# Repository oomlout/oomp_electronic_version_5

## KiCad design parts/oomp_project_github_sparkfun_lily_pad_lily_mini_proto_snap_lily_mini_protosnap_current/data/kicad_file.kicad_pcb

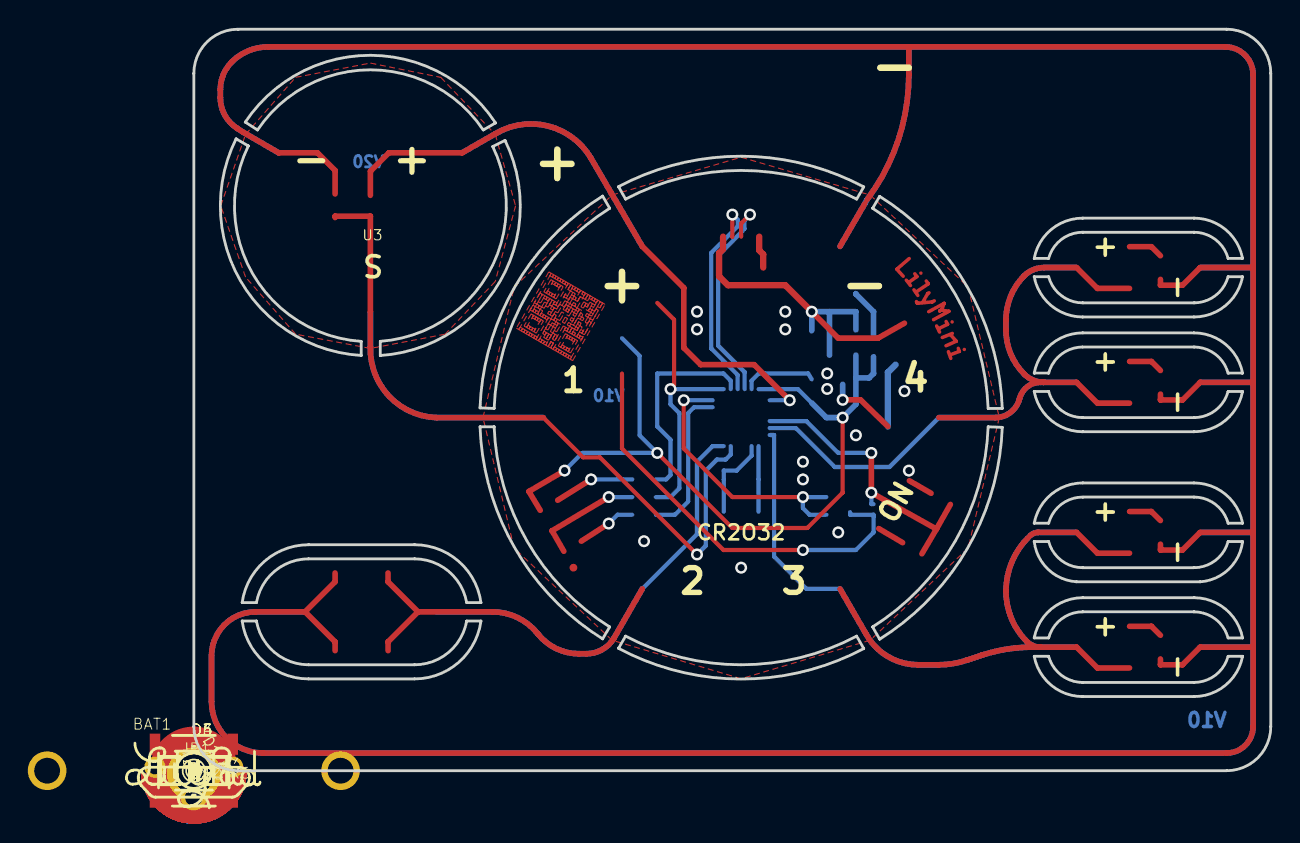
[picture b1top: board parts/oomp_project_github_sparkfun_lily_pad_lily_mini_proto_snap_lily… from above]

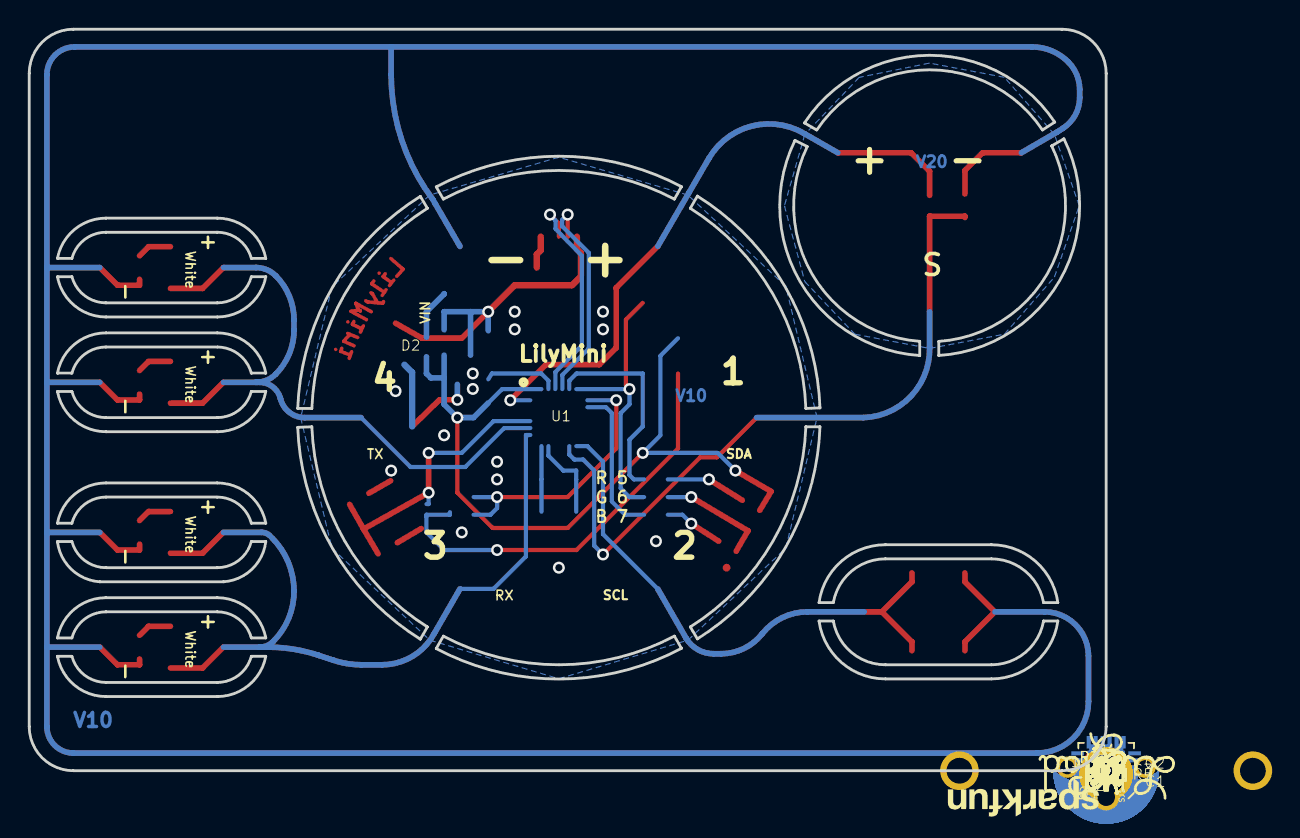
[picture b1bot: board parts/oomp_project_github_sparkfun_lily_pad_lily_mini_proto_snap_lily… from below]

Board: 2 copper layers, 77.5 x 53.3 mm, 170 parts (35 on the bottom side), 27 nets.

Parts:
$1_61_$_2016-09-25_21-56-09: OSHW-LOGOS; OSHW-LOGO-S
BAT1: CR2032; BATTERY_20MM_PTH_KIT
C1, C2: 15pF; 0603-CAP
C3, C4: 0.1uF; 0603-CAP
D1: P-LCC-4-3
D2: RB751; SOD-523
D3, D4, D5, D6: LED-1206
FD1, FD2, FD3, FD4: FIDUCIAL1X2; FIDUCIAL-1X2
FRAME1: FRAME-LETTER; CREATIVE_COMMONS
JP1: USB-B-MICRO-SMD_VERT
JP2: 1X01NS
JP3: 1X01_POGOPIN_PAD_NOSILK_1SIDE_SQUARE
JP4, JP5, JP6, JP7, JP8, JP9: 1X01_POGOPIN_PAD_NOSILK_1SIDE_ROUND
JP12, JP13: PETAL-MEDIUM-2SIDE
JP20, JP21, JP22, JP23, JP24, JP25, JP26, JP27: PETAL-SMALL-2SIDE
LOGO1: LOGO-L
LOGO2: LOGO-L-TOP
LOGO3: OSHW-LOGOS; OSHW-LOGO-S
LOGO4: SFE_LOGO_NAME.1_INCH; SFE_LOGO_NAME_.1
Q1: ZXMP6A13F; SOT23-3
R1, R6: 10K; 0603-RES
R2, R5: 330; 0603-RES
R3: 2K; 0603-RES
R4: 1K; 0603-RES
R7, R8, R9, R10: 150; 0603-RES
S1: TACTILE_SWITCH_SMD_4.6X2.8MM
S2: TACTILE-SWITCH-SMD
SEWTAP1, SEWTAP2, SEWTAP3, SEWTAP4: PETAL-MEDIUM-2SIDE
SEWTAP+0: PETAL-MEDIUM-2SIDE
SEWTAP-0: PETAL-MEDIUM-2SIDE
SEWTAPLS+0: PLUS; PETAL-SMALL-2SIDE
SEWTAPLS-0: MINUS; PETAL-SMALL-2SIDE
SEWTAPLSOUT0: OUT; PETAL-SMALL-2SIDE
SJ1: PAD-JUMPER-2-NO_NO_SILK
ST1, ST2, ST3: PETAL-NOHOLE-2SIDE
U1: SAMD11D14A-M; QFN-24_ALT2
U2: AP2112K-3.3V; SOT23-5
U3: ALS-PT19
U$1: LOGO-LILYPAD
U$2: LOGO-LPLP; LOGO-LILYPAD
U$4: SFE_LOGO_FLAME_COPPER_EXPOSED_.1
U$5, U$6, U$7, U$8, U$9: LOGO-L
UNK_HOLE_0: dummyfp0
UNK_HOLE_1: dummyfp1
UNK_HOLE_2: dummyfp2
UNK_HOLE_3: dummyfp3
UNK_HOLE_4: dummyfp4
UNK_HOLE_5: dummyfp5
UNK_HOLE_6: dummyfp6
UNK_HOLE_7: dummyfp7
UNK_HOLE_8: dummyfp8
UNK_HOLE_9: dummyfp9
UNK_HOLE_10: dummyfp10
UNK_HOLE_11: dummyfp11
UNK_HOLE_12: dummyfp12
UNK_HOLE_13: dummyfp13
UNK_HOLE_14: dummyfp14
UNK_HOLE_15: dummyfp15
UNK_HOLE_16: dummyfp16
UNK_HOLE_17: dummyfp17
UNK_HOLE_18: dummyfp18
UNK_HOLE_19: dummyfp19
UNK_HOLE_20: dummyfp20
UNK_HOLE_21: dummyfp21
UNK_HOLE_22: dummyfp22
UNK_HOLE_23: dummyfp23
UNK_HOLE_24: dummyfp24
UNK_HOLE_25: dummyfp25
UNK_HOLE_26: dummyfp26
UNK_HOLE_27: dummyfp27
UNK_HOLE_28: dummyfp28
UNK_HOLE_29: dummyfp29
UNK_HOLE_30: dummyfp30
UNK_HOLE_31: dummyfp31
UNK_HOLE_32: dummyfp32
UNK_HOLE_33: dummyfp33
UNK_HOLE_34: dummyfp34
UNK_HOLE_35: dummyfp35
UNK_HOLE_36: dummyfp36
UNK_HOLE_37: dummyfp37
UNK_HOLE_38: dummyfp38
UNK_HOLE_39: dummyfp39
UNK_HOLE_40: dummyfp40
UNK_HOLE_41: dummyfp41
UNK_HOLE_42: dummyfp42
UNK_HOLE_43: dummyfp43
UNK_HOLE_44: dummyfp44
UNK_HOLE_45: dummyfp45
UNK_HOLE_46: dummyfp46
UNK_HOLE_47: dummyfp47
UNK_HOLE_48: dummyfp48
UNK_HOLE_49: dummyfp49
UNK_HOLE_50: dummyfp50
UNK_HOLE_51: dummyfp51
UNK_HOLE_52: dummyfp52
UNK_HOLE_53: dummyfp53
UNK_HOLE_54: dummyfp54
UNK_HOLE_55: dummyfp55
UNK_HOLE_56: dummyfp56
UNK_HOLE_57: dummyfp57
UNK_HOLE_58: dummyfp58
UNK_HOLE_59: dummyfp59
UNK_HOLE_60: dummyfp60
UNK_HOLE_61: dummyfp61
UNK_HOLE_62: dummyfp62
UNK_HOLE_63: dummyfp63
UNK_HOLE_64: dummyfp64
UNK_HOLE_65: dummyfp65
UNK_HOLE_66: dummyfp66
UNK_HOLE_67: dummyfp67
UNK_HOLE_68: dummyfp68
UNK_HOLE_69: dummyfp69
UNK_HOLE_70: dummyfp70
UNK_HOLE_71: dummyfp71
UNK_HOLE_72: dummyfp72
UNK_HOLE_73: dummyfp73
UNK_HOLE_74: dummyfp74
UNK_HOLE_75: dummyfp75
UNK_HOLE_76: dummyfp76
UNK_HOLE_77: dummyfp77
UNK_HOLE_78: dummyfp78
UNK_HOLE_79: dummyfp79
UNK_HOLE_80: dummyfp80
UNK_HOLE_81: dummyfp81
UNK_HOLE_82: dummyfp82
UNK_HOLE_83: dummyfp83
UNK_HOLE_84: dummyfp84
UNK_HOLE_85: dummyfp85
UNK_HOLE_86: dummyfp86
UNK_HOLE_87: dummyfp87
UNK_HOLE_88: dummyfp88
UNK_HOLE_89: dummyfp89
UNK_HOLE_90: dummyfp90
UNK_HOLE_91: dummyfp91
Y1: 32.768kHz; CRYSTAL-SMD-3.2X1.5MM

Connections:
B: D1.3, R2.2
BATT3V: BAT1.+1, BAT1.+2, JP9.P$1, Q1.3
BUTTON: S1.1, S1.2, SJ1.1, U1.4
G: D1.2, R3.2
GND: BAT1.-3, C1.1, C2.1, C3.2, C4.2, JP1.GND, JP4.P$1, JP13.1, JP21.1, JP23.1, JP25.1, JP27.1, R1.1, R6.1, R7.1, R8.1, R9.1, R10.1, S1.3, S1.4, S2.3, S2.4, SEWTAP-0.1, SEWTAPLS-0.1, U1.23, U2.2
unnamed: D2.A, U2.5
unnamed: D3.C, R7.2
unnamed: D4.C, R8.2
unnamed: D5.C, R9.2
unnamed: D6.C, R10.2
R: D1.1, R4.2
SEWTAP1: R6.2, SEWTAP1.1, SEWTAPLSOUT0.1, U1.11, U3.E
SEWTAP2: JP12.1, S2.1, S2.2, SEWTAP2.1, U1.12
SEWTAP3: D3.A, D4.A, JP20.1, JP22.1, SEWTAP3.1, U1.6
SEWTAP4: D5.A, D6.A, JP24.1, JP26.1, SEWTAP4.1, U1.5
SEWTAP+: SEWTAP+0.1, SEWTAPLS+0.1, U1.1, U3.C
USB5V: JP1.VBUS, JP2.1, Q1.1, R1.2, U2.1, U2.3
USB_N: JP1.D-, U1.21
USB_P: JP1.D+, U1.22
VDD: C4.1, D1.4, D2.C, JP6.P$1, Q1.2, U1.24
X1: C1.2, U1.7, Y1.P$2
X2: C2.2, U1.8, Y1.P$1
~BLUE/SWDIO: JP7.P$1, R2.1, U1.20
~GREEN: R3.1, U1.17
~RED/SWDCLK: JP3.P$1, R4.1, U1.19
~RST: JP8.P$1, R5.2, SJ1.2
~RST1: C3.1, R5.1, U1.18

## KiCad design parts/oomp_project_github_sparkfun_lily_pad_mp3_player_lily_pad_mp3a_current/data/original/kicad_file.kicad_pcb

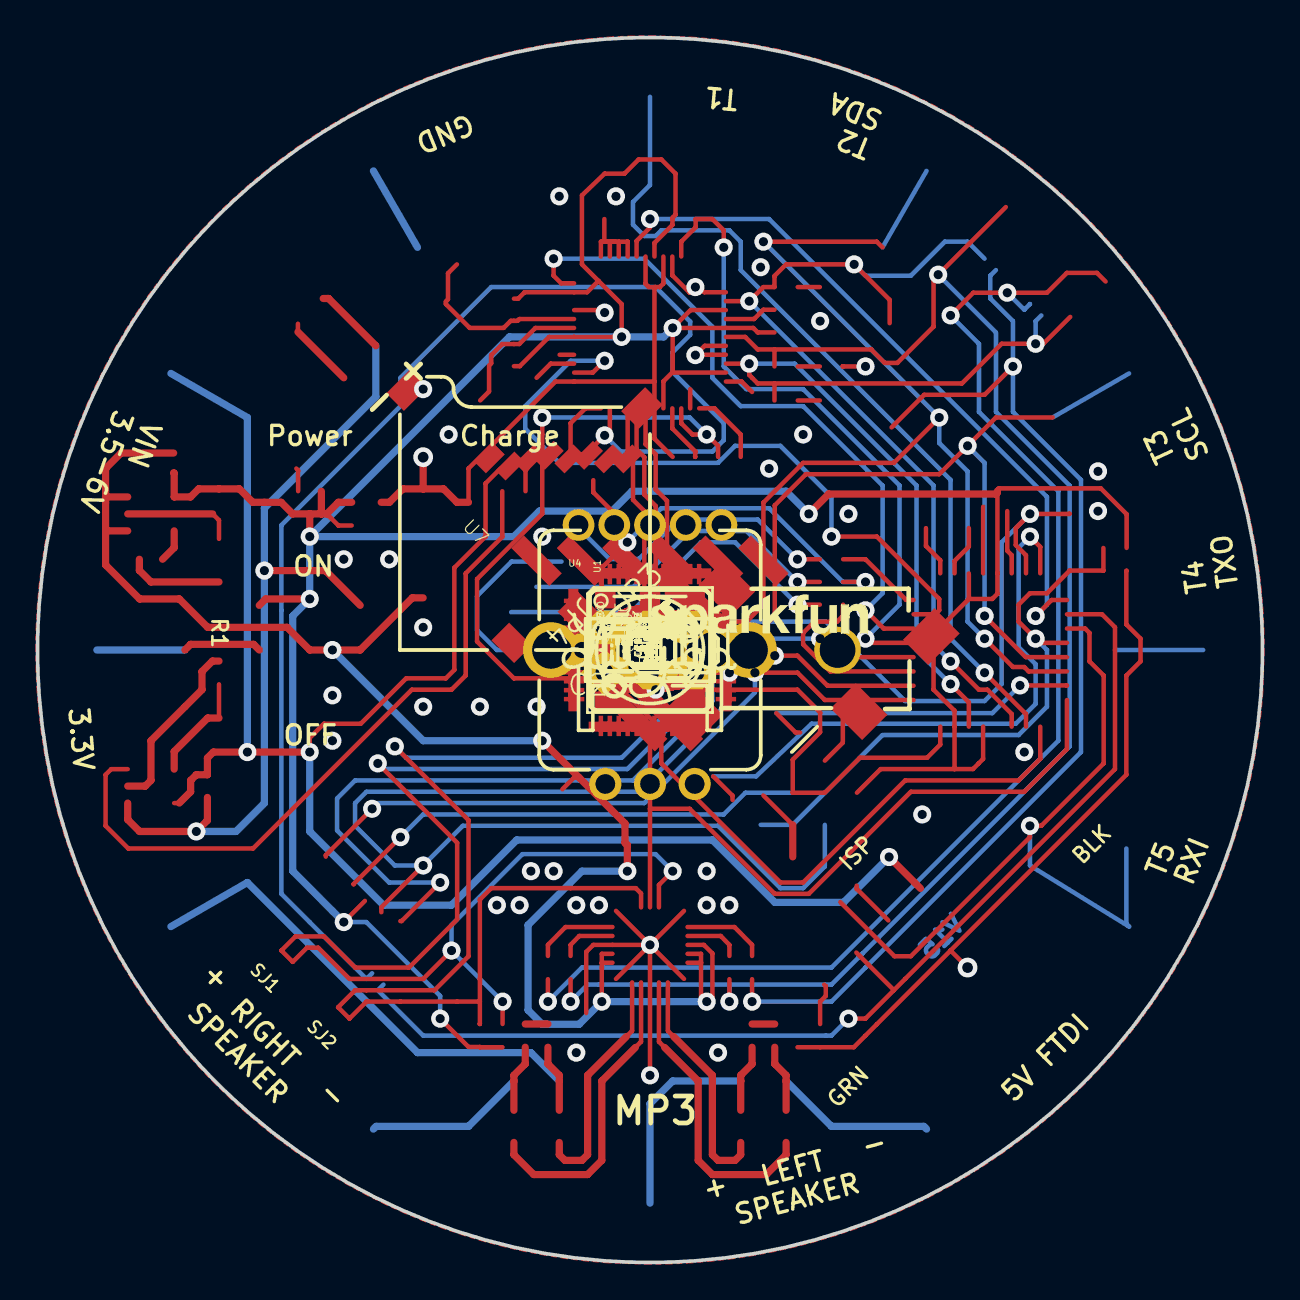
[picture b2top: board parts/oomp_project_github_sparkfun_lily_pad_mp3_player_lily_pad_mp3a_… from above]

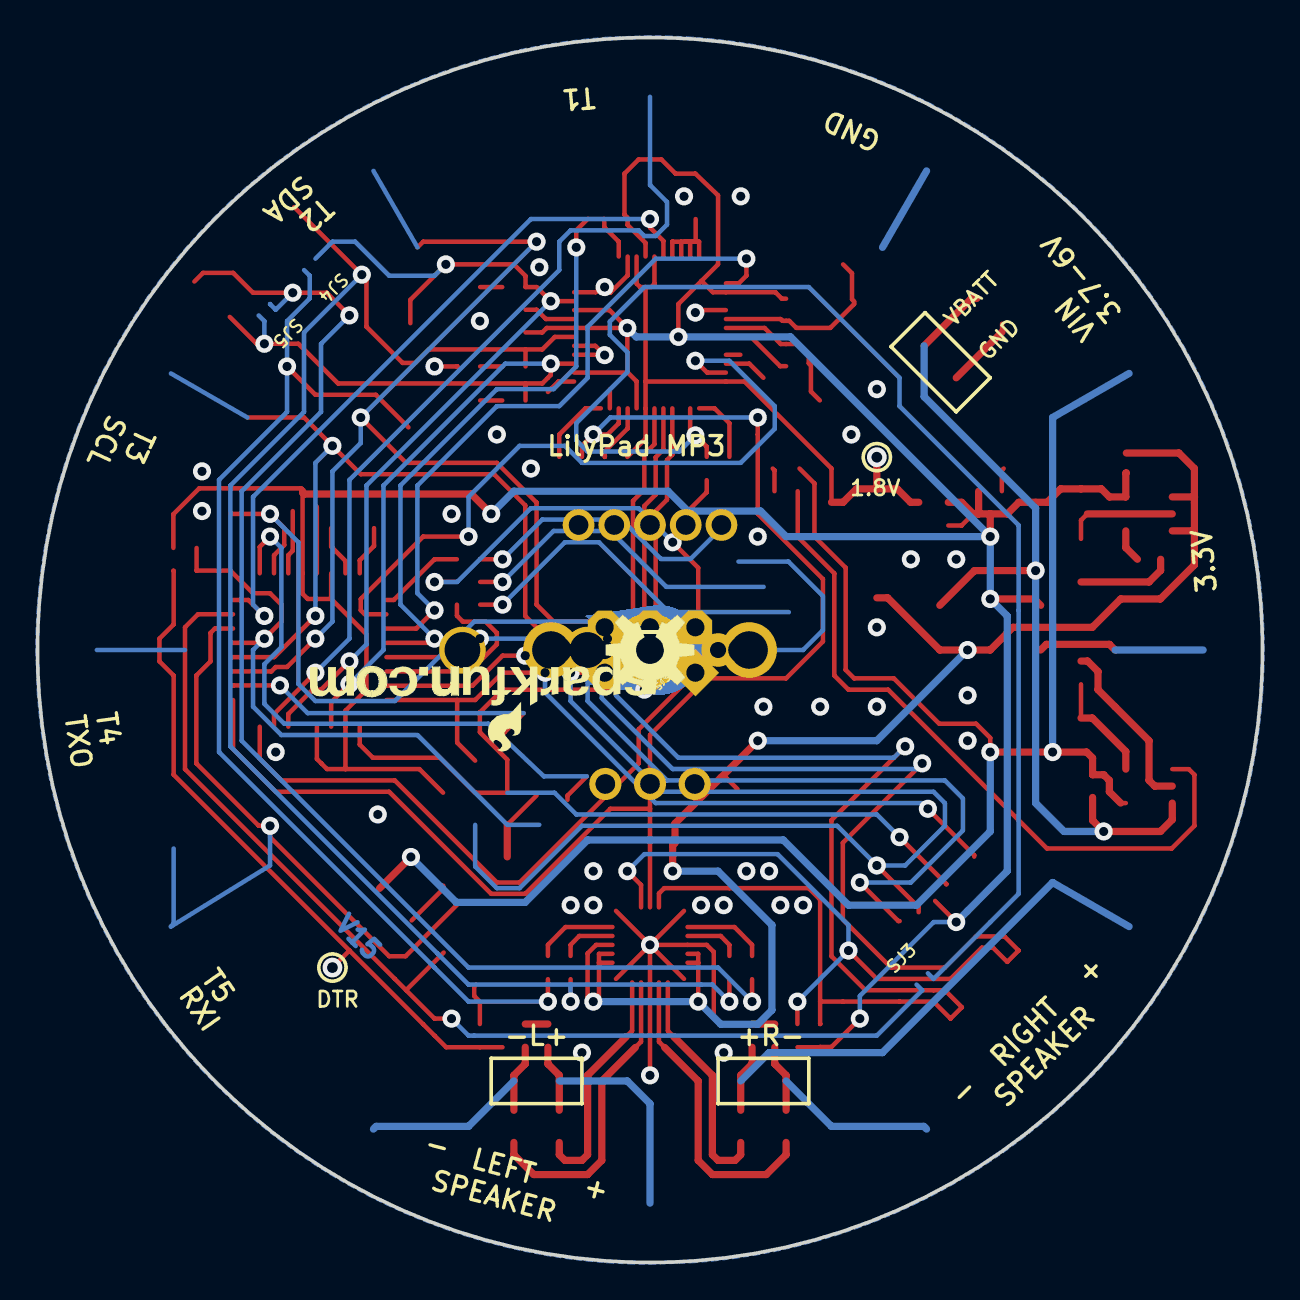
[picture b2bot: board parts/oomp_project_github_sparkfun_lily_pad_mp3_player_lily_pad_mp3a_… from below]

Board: 2 copper layers, 68.6 x 68.6 mm, 121 parts (7 on the bottom side), 69 nets.

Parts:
C1, C4, C6, C8, C18, C19, C20, C21, C23, C24, C25: 0.1uF; 0402-CAP
C2: 47uF; EIA3528
C3, C13, C26, C27, C28, C29: 1uF; 0402-CAP
C5, C7, C22: 10uF; EIA3216
C9, C10: 4.7uF; 0402-CAP
C11, C12: 22pF; 0402-CAP
C14, C15: 10nF; 0402-CAP
C16: 47nF; 0402-CAP
C17: 470pF; 0402-CAP
C30, C31, C32, C33: 1nF; 0402-CAP
D1: SOD-523
JP1: LiPo; JST-2-SMD
JP2: FTDI; 1X06-SMD
JP3: POWER; 1X02
JP4: PROG; 2X3-NS
JP5: HEADPHONE; AUDIO-JACK-3.5MM-SMD
JP6: LOGO-SFENW2; SFE-NEW-WEB
JP7, JP8: FIDUCIALUFIDUCIAL; MICRO-FIDUCIAL
L1, L2, L3, L4: 0805
LED1: RED; LED-0603
LED2: YELLOW; LED-0603
LOGO1, LOGO3: LOGO-SFESK; SFE-LOGO-FLAME
LOGO2: LOGO-SFENEW; SFE-NEW-WEBLOGO
R1, R21: 2K; 0402-RES
R1X0: DNP; AXIAL-0.3
R2, R20: 1K; 0402-RES
R3, R22: 10K; 0402-RES
R4: 1M; 0402-RES
R5, R6, R7, R13, R14, R15, R16: 100k; 0402-RES
R8, R9, R24, R25, R26: 330; 0402-RES
R10, R11: 20; 0402-RES
R12: 10; 0402-RES
R18, R19: 4.7K; 0402-RES
S1: POWER; AYZ0202
S2: EC12PLRGBSDVBF-D; ENCODER_LED_3
SJ1, SJ2, SJ3, SJ4, SJ5: SJ_2S-NO
ST1: TRIG2/SDA; PETAL-LONG-1-2SIDE
ST2: TRIG3/SCL; PETAL-LONG-1-2SIDE
ST3: TRIG4/TXO; PETAL-LONG-1-2SIDE
ST4: TRIG5/RXI; PETAL-LONG-1-2SIDE
ST5: SPKL-; PETAL-LONG-1-2SIDE
ST6: SPKL+; PETAL-LONG-1-2SIDE
ST7: SPKR-; PETAL-LONG-1-2SIDE
ST8: SPKR+; PETAL-LONG-1-2SIDE
ST9: 3.3V; PETAL-LONG-1-2SIDE
ST10: VIN; PETAL-LONG-1-2SIDE
ST11: GND; PETAL-LONG-1-2SIDE
ST12: TRIG1; PETAL-LONG-1-2SIDE
TP1: TRIG1; 1X01NS
TP2: TRIG2/SDA; 1X01NS
TP3: TRIG3/SCL; 1X01NS
TP4: TRIG4/TXO; 1X01NS
TP5: TRIG5/RXI; 1X01NS
TP6: SPKL-; 1X01NS
TP7: SPKL+; 1X01NS
TP8: SPKR-; 1X01NS
TP9: SPKR+; 1X01NS
TP10: 3.3V; 1X01NS
TP11: VIN; 1X01NS
TP12: GND; 1X01NS
TP13: DTR; PAD.03X.05
TP14: 1.8V; PAD.03X.05
U1: ATMEGA328; TQFP32-08
U2: MCP73831; SOT23-5
U3: MIC5219 3.3V; SOT23-5
U4: VS1053; LQFP-48
U5: SP6214 1.8V; SC70
U6: TPA2016D2RTJ; QFN-20-0.5MM
U7: USD-SOCKET; MICRO-SD-SOCKET-PP
U$1: LOGO-LPLP; LOGO-LILYPAD
U$4: OSHW-LOGOM; OSHW-LOGO-M
U$12: CREATIVE_COMMONS
Y1: 8MHz; RESONATOR-SMD
Y2: 12.288MHz; CRYSTAL-SMD-5X3

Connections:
1.8V: C7.A, C8.1, C21.1, TP14.P$1, U4.5, U4.7, U4.24, U4.31, U5.5
3.3V: C1.1, C3.1, C5.A, C6.1, C18.1, C19.1, C20.1, D1.A, JP4.2, R3.2, R5.2, R7.1, R8.2, R18.1, R19.1, S1.4, S2.5, U1.4, U1.6, U1.18, U1.20, U3.5, U4.6, U4.14, U4.19, U4.32, U4.38, U4.43, U4.45, U5.1, U5.3, U7.4
3.3V-TAP: S1.5, ST9.1, TP10.1
AMP-L: C28.1, JP5.TSH, SJ4.1
AMP-LX: C26.2, U6.1
AMP-R: C26.1, JP5.RSH, SJ5.1
AMP-RX: C28.2, U6.15
DTR: C4.1, R20.1, R21.2, TP13.P$1
EN-GPIO1: R13.2, U1.25, U4.34, U6.18
FTDI-DTR: JP2.1, R20.2
FTDI-RXI: JP2.3, R22.2
G1: R6.2, U4.9, U4.10, U4.11, U4.12
G2: R15.2, U4.25
GBUF: C27.1, C29.1, JP5.SLEEVE, R12.2, U4.42
GBUFLX: C27.2, U6.2
GBUFRX: C29.2, U6.14
GND: C1.2, C2.C, C3.2, C5.C, C6.2, C7.C, C8.2, C9.2, C10.2, C11.1, C12.1, C13.1, C14.2, C15.2, C16.2, C17.2, C18.2, C19.2, C20.2, C21.2, C22.C, C23.2, C24.2, C25.2, C30.2, C31.2, C32.2, C33.2, JP1.1, JP2.5, JP2.6, JP3.1, JP4.6, LED1.C, R1.2, R1X0.P$2, R2.1, R6.1, R13.1, R14.1, R15.1, R16.1, R21.1, S2.C, ST11.1, TP12.1, U1.3, U1.5, U1.21, U2.2, U3.2, U4.4, U4.16, U4.20, U4.21, U4.22, U4.35, U4.37, U4.40, U4.41, U4.47, U5.2, U6.3, U6.8, U6.PAD, U7.6, U7.CD1, U7.CD2, U7.GND1, U7.GND3, Y1.2
GPIO0: R14.2, U4.33
LEFT: JP5.TIP, R10.2, SJ4.2, U1.22, U4.46
MISO: JP4.1, U1.16, U4.30, U7.7
MOSI: JP4.4, U1.15, U4.29, U7.3
MP3-CS: U1.10, U4.23
MP3-DCS: U1.11, U4.13
MP3-DREQ: U1.32, U4.8
MP3-MIDI-RX: R5.1, SJ3.1, U4.26
MP3-RST: R7.2, U1.12, U4.3
unnamed: U1.7, Y1.1
unnamed: U1.8, Y1.3
unnamed: C13.2, U4.44
unnamed: C16.1, R12.1
unnamed: LED1.A, R8.1
unnamed: C15.1, R10.1
unnamed: LED2.C, R9.2
unnamed: C11.2, R4.2, U4.18, Y2.3
unnamed: C12.2, R4.1, U4.17, Y2.1
unnamed: C14.1, R11.1
unnamed: R24.2, S2.1
unnamed: R25.2, S2.2
unnamed: R26.2, S2.4
unnamed: L1.1, U6.6
unnamed: L2.1, U6.7
unnamed: L3.1, U6.10
unnamed: L4.1, U6.9
unnamed: C17.1, U3.4
unnamed: R16.2, U4.36
PROG: R1.1, R1X0.P$1, U2.5
RIGHT: JP5.RING, R11.2, SJ5.2, U1.19, U4.39
ROT-A: C24.1, S2.A, U1.1
ROT-B: C25.1, S2.B, U1.26
ROT-LEDB: R26.1, U1.9
ROT-LEDG: R25.1, U1.24
ROT-LEDR: R24.1, U1.14
ROT-SW: R2.2, S2.3, U1.2
RST: C4.2, JP4.5, R3.1, U1.29
SCK: JP4.3, U1.17, U4.28, U7.5
SD-CS: U1.13, U7.2
SPKL+: C32.1, L3.2, ST6.1, TP7.1
SPKL-: C33.1, L4.2, ST5.1, TP6.1
SPKR+: C30.1, L1.2, ST8.1, TP9.1
SPKR-: C31.1, L2.2, ST7.1, TP8.1
STAT: R9.1, U2.1
TRIG1: ST12.1, TP1.1, U1.23
TRIG2/SDA: R18.2, SJ2.1, SJ2.2, ST1.1, TP2.1, U1.27, U6.19
TRIG3/SCL: R19.2, SJ1.1, SJ1.2, ST2.1, TP3.1, U1.28, U6.17
TRIG4/TXO: JP2.2, SJ3.2, ST3.1, TP4.1, U1.31
TRIG5/RXI: R22.1, ST4.1, TP5.1, U1.30
VBATT: C10.1, JP1.2, JP3.2, S1.1, U2.3
VBATT_SW: C2.A, C22.A, C23.1, D1.C, S1.2, U3.1, U3.3, U6.4, U6.5, U6.11, U6.12, U6.13
VIN: C9.1, JP2.4, LED2.A, ST10.1, TP11.1, U2.4

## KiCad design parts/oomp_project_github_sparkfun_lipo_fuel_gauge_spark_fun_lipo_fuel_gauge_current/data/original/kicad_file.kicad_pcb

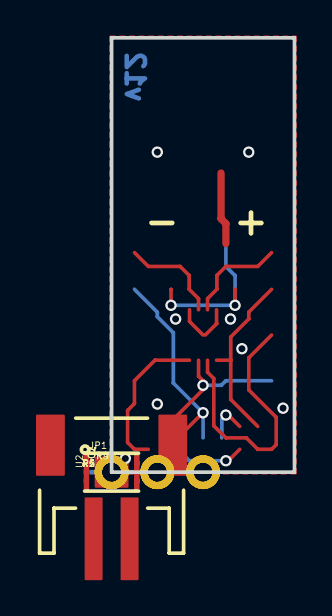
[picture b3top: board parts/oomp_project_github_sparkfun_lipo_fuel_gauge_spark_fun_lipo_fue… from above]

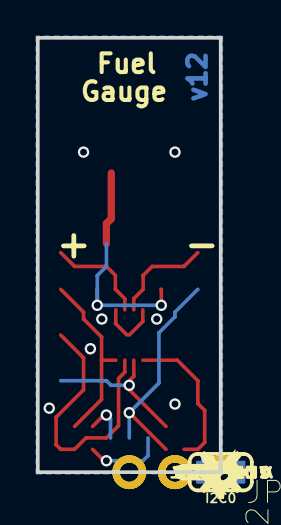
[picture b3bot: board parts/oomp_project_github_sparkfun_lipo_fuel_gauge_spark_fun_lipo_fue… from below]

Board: 2 copper layers, 10.2 x 24.1 mm, 29 parts (15 on the bottom side), 11 nets.

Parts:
C1: 1.0uF; 0402-TIGHT
C2: 10nF; 0402-TIGHT
FRAME1: FRAME-LETTER; CREATIVE_COMMONS
I2C0: JUMPER-SMT_3_2-NC_TRACE_SILK; SMT-JUMPER_3_2-NC_TRACE_SILK
JP1: input; JST-2-SMD
JP2, JP4: 1X03_NO_SILK
JP3: SFE_LOGO_FLAME.1_INCH; SFE_LOGO_FLAME_.1
JP5: 1X02_NO_SILK
JP6, JP7, JP8, JP9: FIDUCIALUFIDUCIAL; FIDUCIAL-MICRO
LOGO1: SFE_LOGO_NAME_FLAMEBLANK; BLANK
R1: 1k; 0402-TIGHT
R2: 100; 0402-TIGHT
R3, R4, R5, R6: 2.2k; 0402-TIGHT
U2: MAX1704X; TDFN-8
U$1: OSHW-LOGOS; OSHW-LOGO-S
U$2: SDA0
U$3: SCL0
U$4: QST0
U$5: VCC0
U$6: GND0
U$7: ALT0
U$8: #I2C#0

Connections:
ALT: JP4.3, R3.1, U2.5
GND: C1.2, C2.2, JP1.1, JP4.2, JP5.2, R4.1, U2.1, U2.4, U2.EP
unnamed: I2C0.3, R6.2
unnamed: C1.1, R1.2, U2.2
unnamed: I2C0.1, R5.2
QST: JP2.3, R4.2, U2.6
SCL: JP2.2, R5.1, U2.7
SDA: JP2.1, R6.1, U2.8
VCC: I2C0.2, JP4.1, R3.2
VDD: C2.1, R2.1, U2.3
V_BATT: JP1.2, JP5.1, R1.1, R2.2

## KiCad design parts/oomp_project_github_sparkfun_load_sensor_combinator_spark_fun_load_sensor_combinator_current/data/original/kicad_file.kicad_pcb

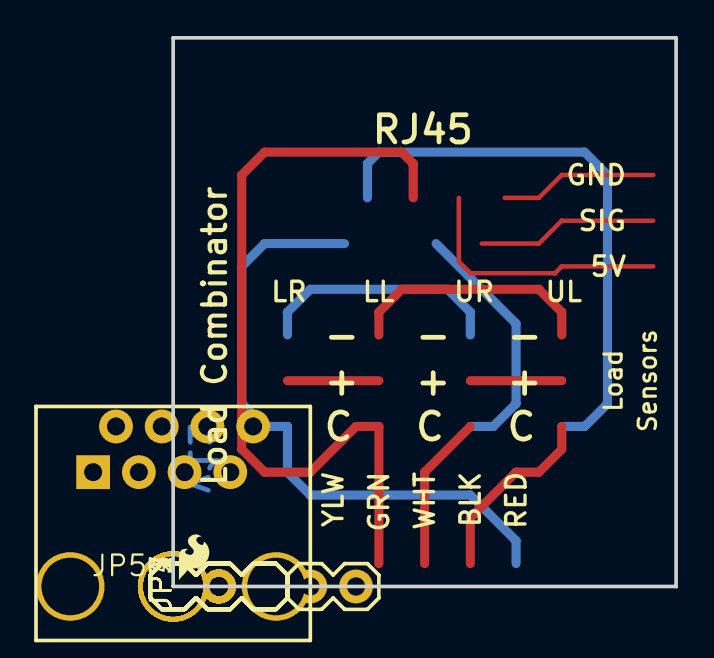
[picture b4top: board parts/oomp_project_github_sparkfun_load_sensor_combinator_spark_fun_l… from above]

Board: 2 copper layers, 27.9 x 30.5 mm, 14 parts (1 on the bottom side), 11 nets.

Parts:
FRAME1: CREATIVE_COMMONS
JP1: UL; 1X03
JP2: UR; 1X03
JP3: LL; 1X03
JP4: LR; 1X03
JP5: 1X05
JP6: RJ45; RJ45-8
JP7: 1X03
LOGO3: SFE_LOGO_FLAME.1_INCH; SFE_LOGO_FLAME_.1
STANDOFF1, STANDOFF2, STANDOFF3, STANDOFF4: STAND-OFF
U$7: OSHW-LOGOS; OSHW-LOGO-S

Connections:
5V: JP6.3, JP7.3
A+: JP3.3, JP5.4, JP6.5
A-: JP2.3, JP5.3, JP6.4
E+: JP4.3, JP5.1, JP6.8
E-: JP1.3, JP5.2, JP6.7
GND: JP6.1, JP7.1
unnamed: JP2.1, JP4.1
unnamed: JP1.1, JP3.1
unnamed: JP3.2, JP4.2
unnamed: JP1.2, JP2.2
TEMP_DAT: JP6.2, JP7.2

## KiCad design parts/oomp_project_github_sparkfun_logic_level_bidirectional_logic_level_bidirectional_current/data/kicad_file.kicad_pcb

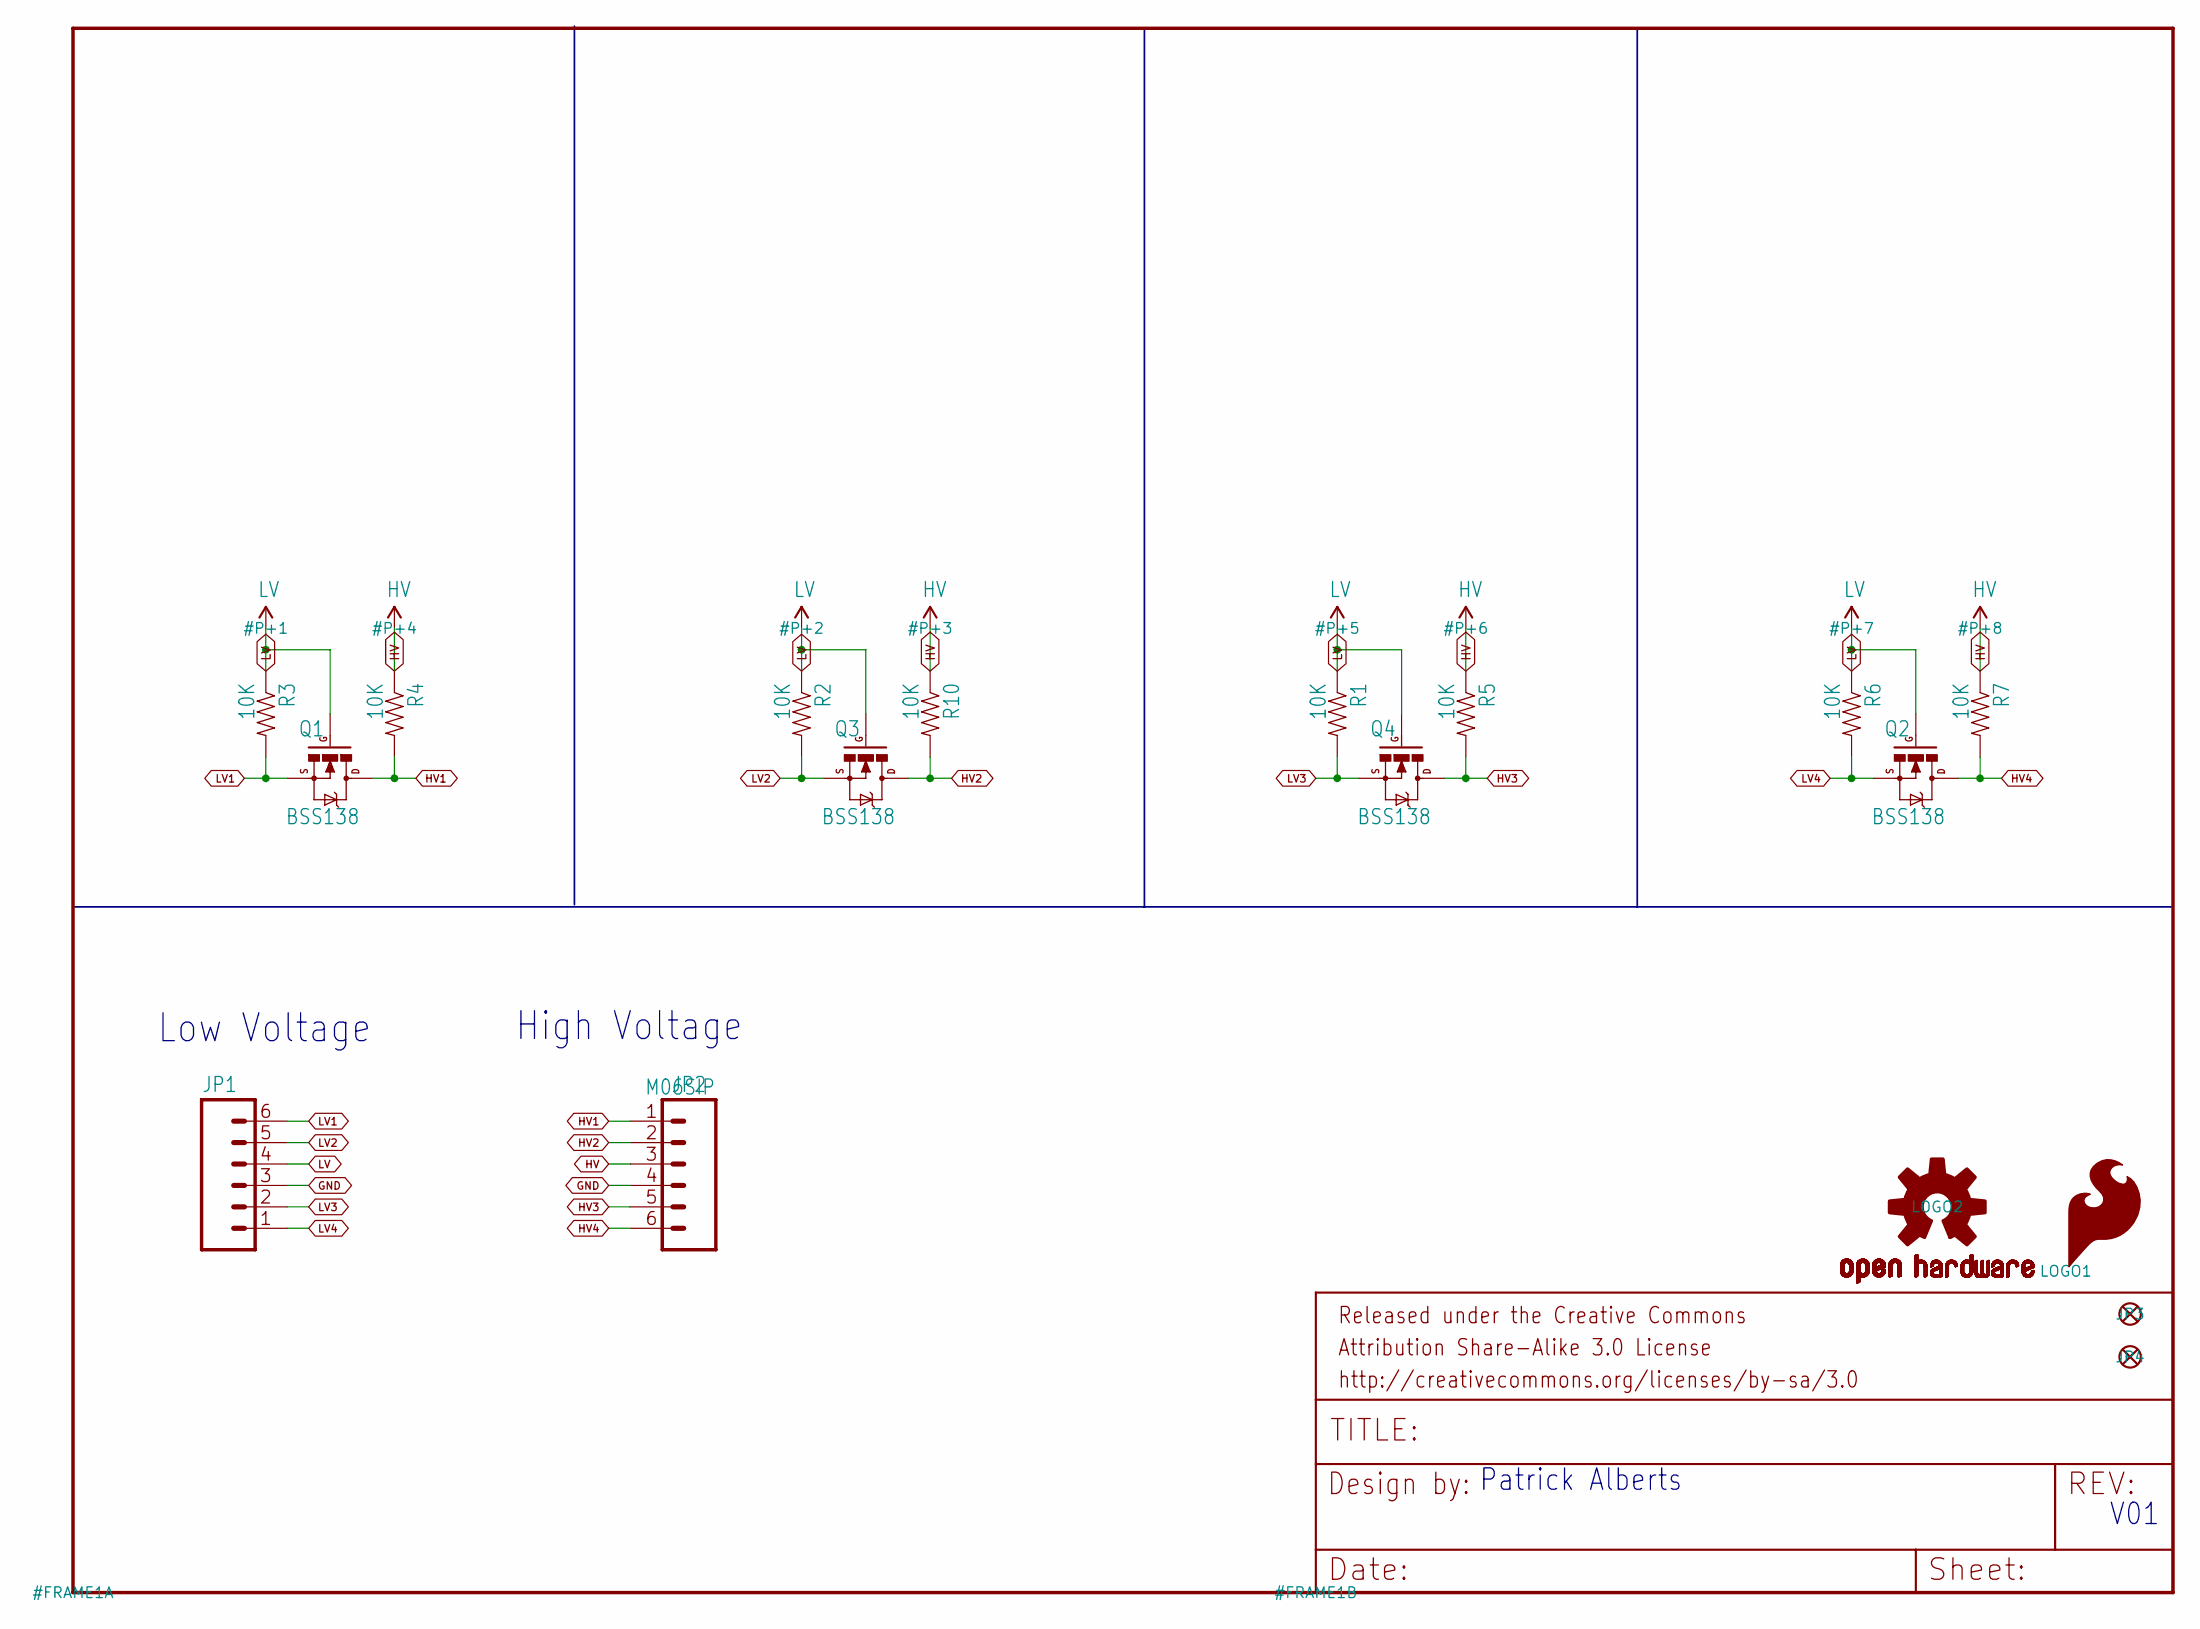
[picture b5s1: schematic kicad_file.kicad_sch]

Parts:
JP1, JP2: M06SIP; 1X06
JP3, JP4: FIDUCIALUFIDUCIAL; MICRO-FIDUCIAL
LOGO1: SFE_LOGO_FLAME.1_INCH; SFE_LOGO_FLAME_.1
LOGO2: OSHW-LOGOS; OSHW-LOGO-S
Q1, Q2, Q3, Q4: BSS138; SOT23-3
R1, R2, R3, R4, R5, R6, R7, R10: 10K; 0603-RES

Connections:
GND: JP1.3, JP2.4
HV: JP2.3, R4.1, R5.1, R7.1, R10.1
HV1: JP2.1, Q1.3 (D), R4.2
HV2: JP2.2, Q3.3 (D), R10.2
HV3: JP2.5, Q4.3 (D), R5.2
HV4: JP2.6, Q2.3 (D), R7.2
LV: JP1.4, Q1.1 (G), Q2.1 (G), Q3.1 (G), Q4.1 (G), R1.1, R2.1, R3.1, R6.1
LV1: JP1.6, Q1.2 (S), R3.2
LV2: JP1.5, Q3.2 (S), R2.2
LV3: JP1.2, Q4.2 (S), R1.2
LV4: JP1.1, Q2.2 (S), R6.2

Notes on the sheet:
V01
Low Voltage
Patrick Alberts
High Voltage

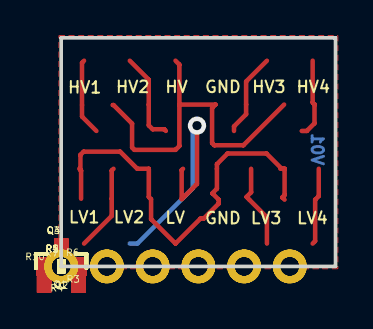
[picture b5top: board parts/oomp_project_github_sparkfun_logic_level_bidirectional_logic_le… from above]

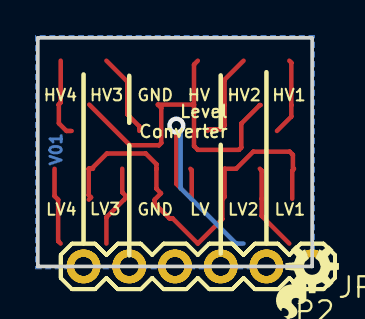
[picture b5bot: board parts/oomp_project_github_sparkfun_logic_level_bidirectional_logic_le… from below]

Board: 2 copper layers, 15.2 x 12.7 mm, 18 parts (4 on the bottom side), 11 nets.

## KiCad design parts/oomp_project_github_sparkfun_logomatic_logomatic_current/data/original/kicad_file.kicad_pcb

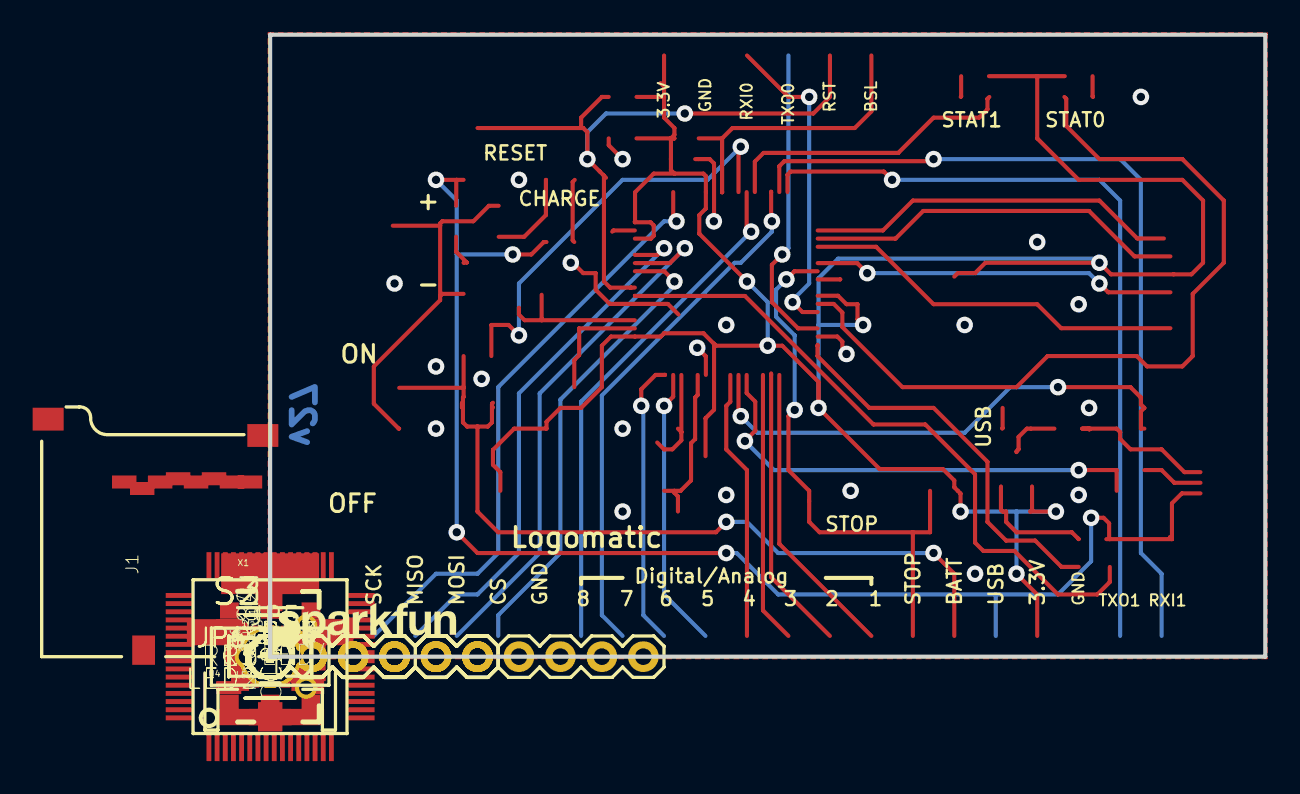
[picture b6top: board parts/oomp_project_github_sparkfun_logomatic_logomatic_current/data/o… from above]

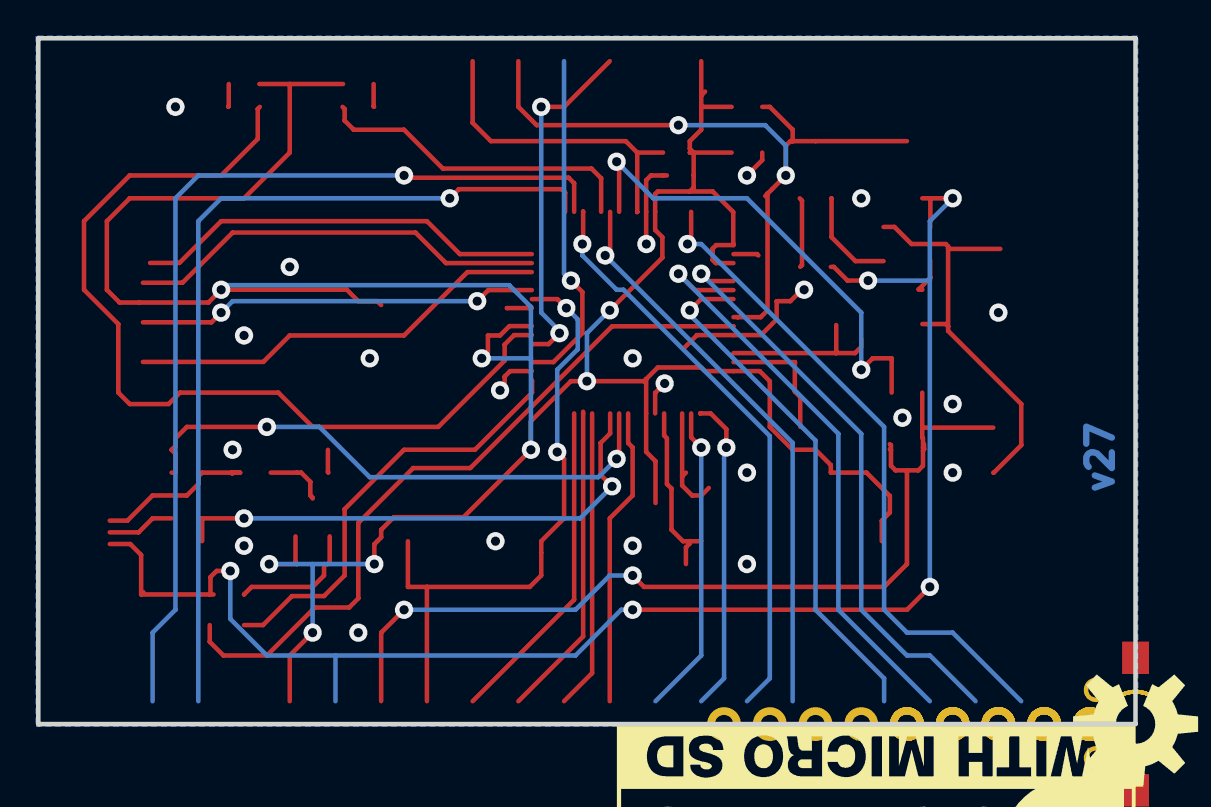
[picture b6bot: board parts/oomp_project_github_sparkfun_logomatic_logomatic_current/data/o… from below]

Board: 2 copper layers, 61.0 x 38.1 mm, 71 parts (3 on the bottom side), 52 nets.

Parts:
C1, C2, C7, C8, C9, C10, C11, C12: 0.1uF; 0603-CAP
C3, C4: 18pF; 0603-CAP
C5, C17: 4.7uF; 0603-CAP
C6: 10uF; EIA3216
C13, C14, C15, C16: 22pF; 0603-CAP
FRAME2, FRAME4: FRAME-LETTER; CREATIVE_COMMONS
J1: USD_CONNECTOR; MICRO-SD-SOCKET-PP
JP1: Prog; 1X06
JP2: LiPo; JST-2-SMD
JP4: 1X04
JP5: 1X06
JP6: M100.1; 1X10
LED1: LED RED; LED-0603
LED2: RED; LED-0603
LED3: LED-0603
LED4: GREEN; LED-0603
LOGO1: OSHW-LOGOL; OSHW-LOGO-L
LOGO2: SFE_LOGO_NAME.1_INCH; SFE_LOGO_NAME_.1
LOGO3: SFE_LOGO_FLAME.4_INCH; SFE_LOGO_FLAME_.4
Q1: 12MHz; CRYSTAL-SMD-5X3
Q2: 32kHz; CRYSTAL-32KHZ-SMD
Q4: TRANSISTOR_PNPSMD; SOT23-3
R1, R6, R7: 10K; 0603-RES@1
R2: 2.0k; 0603-RES
R3, R4, R5, R15: 330; 0603-RES
R8, R13: 10k; 0603-RES@1
R9, R10: 33; 0603-RES
R11: 1.5k; 0603
R12: 1k; 0603-RES@1
R14: 100k; 0603-RES@1
R16, R17: 1M; 0603-RES@1
R18, R19, R20: 100k; 0603-RES
S1: AYZ0202
S2: Stop; TACTILE_SWITCH_SMD
S3: Reset; TACTILE_SWITCH_SMD
U1: MCP73831; SOT23-5
U2: 3.3V; SOT23-5
U4: LPC213X; SQFP-S-10X10-64
U$1, U$2: FIDUCIAL1X2; FIDUCIAL-1X2
U$3, U$4, U$5, U$8: STAND-OFF
U$6: LOGOMATIC_LOGO
U$7: LOGO-SFESK; SFE-LOGO-FLAME
U$10: REVISION
X1: USB_MICROB_PLUGCONN-11752; USB-B-MICRO-SMD_V03

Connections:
BATTLVL: R16.2, R17.1, U4.39
BSL: JP1.1, R7.2, U4.41
CS1: JP4.1, U4.55
GND: C1.2, C2.2, C3.2, C4.2, C5.2, C6.C, C7.2, C8.2, C9.2, C10.2, C11.2, C12.2, C13.1, C14.1, C15.1, C16.1, C17.2, J1.GND, J1.GND1, J1.GND3, JP1.5, JP2.1, JP5.4, JP6.10, R2.1, R14.1, R15.1, R17.2, S2.1, S3.1, S3.2, U1.2, U2.2, U4.6, U4.18, U4.25, U4.42, U4.50, U4.59, X1.GND1
MISO0: J1.DO, U4.29
MISO1: JP4.3, U4.53
MOSI0: J1.DI, U4.30
MOSI1: JP4.2, U4.54
unnamed: R2.2, U1.5
unnamed: J1.CD1, R18.1
unnamed: J1.RSV1, R20.1
unnamed: C13.2, Q1.3, U4.62
unnamed: C16.2, Q2.X2, U4.3
unnamed: LED2.A, R4.2
unnamed: C15.2, Q2.X1, U4.5
unnamed: J1.RSV2, R19.1
unnamed: LED1.C, U1.1
unnamed: LED1.A, R3.1
unnamed: R8.1, U4.58
unnamed: Q4.1, R12.2, R13.1
unnamed: LED4.A, R5.2
unnamed: C14.2, Q1.1, U4.61
unnamed: R12.1, U4.17
unnamed: LED3.C, R15.2
P1: JP6.2, U4.15
P2: JP6.3, U4.14
P3: JP6.4, U4.13
P4: JP6.5, U4.9
P5: JP6.6, U4.2
P6: JP6.7, U4.1
P7: JP6.8, U4.35
P8: JP6.9, U4.38
P-D+: C3.1, R9.1, U4.10
P-D-: C4.1, R10.1, U4.11
RAW: JP5.1, R16.1, S1.1, U2.1, U2.3
RST: JP1.2, R1.1, S3.3, S3.4, U4.57
RXI-0: JP1.4, U4.21
RXI-1: JP5.6, U4.34
SCK0: J1.SCLK, U4.27
SCK1: JP4.4, U4.47
STAT: LED3.A, Q4.3, R11.1
STAT0: LED2.C, U4.22
STAT1: LED4.C, U4.37
STOP: C1.1, JP6.1, R6.1, S2.3, U4.26
TXO-0: JP1.3, U4.19
TXO-1: JP5.5, U4.33
USB_D+: R9.2, R11.2, X1.D+1
USB_D-: R10.2, X1.D-1
USB_VIN: C2.1, C17.1, JP5.2, R3.2, R8.2, R14.2, U1.4, X1.VBUS1
VCC: C6.A, C7.1, C8.1, C9.1, C10.1, C11.1, C12.1, J1.VCC, JP1.6, JP5.3, Q4.2, R1.2, R4.1, R5.1, R6.2, R7.1, R13.2, R18.2, R19.2, R20.2, U2.5, U4.7, U4.23, U4.43, U4.49, U4.51, U4.63
VLIPO: C5.1, JP2.2, S1.2, U1.3
~CS0: J1.CS, U4.31

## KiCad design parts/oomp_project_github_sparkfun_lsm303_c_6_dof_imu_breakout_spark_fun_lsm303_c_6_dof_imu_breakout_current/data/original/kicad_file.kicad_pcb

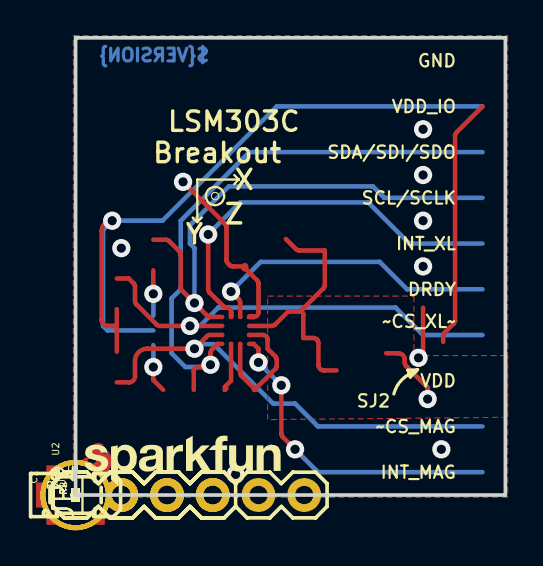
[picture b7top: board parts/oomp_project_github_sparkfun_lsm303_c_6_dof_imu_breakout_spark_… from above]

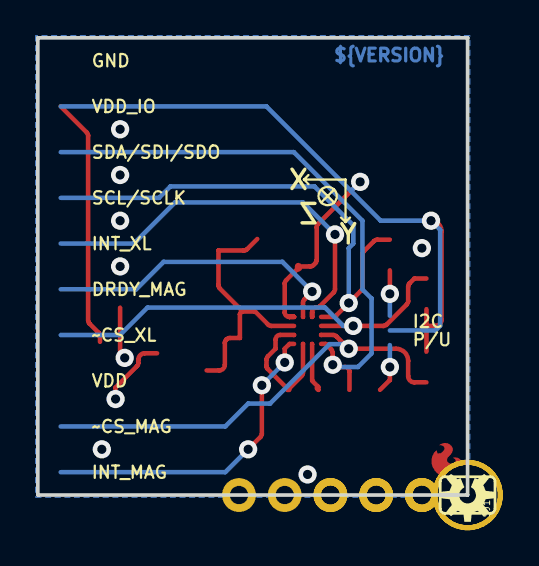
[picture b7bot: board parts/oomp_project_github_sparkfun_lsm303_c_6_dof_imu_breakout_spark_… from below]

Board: 2 copper layers, 23.9 x 25.4 mm, 24 parts (2 on the bottom side), 14 nets.

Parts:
C1: 10uF; EIA3216
C2, C3, C4: 0.1uF; 0603-CAP
FID1, FID2: FIDUCIAL1X2; FIDUCIAL-1X2
FRAME1: FRAME-LETTER; CREATIVE_COMMONS
JP1: 1X04
JP2: 1X06
LOGO1: SFE_LOGO_NAME.1_INCH; SFE_LOGO_NAME_.1
LOGO2: SFE_LOGO_FLAME.1EXP; SFE_LOGO_FLAME_COPPER_EXPOSED_.1
R1: 68; 0603-RES
R2, R5: 4.7K; 0603-RES
R3, R4: 10K; 0603-RES
SJ1: PAD-JUMPER-3-3OF3_NC_BY_TRACE_YES_SILK_FULL_BOX
SJ2: JUMPER-PAD-2-NC_BY_TRACE; PAD-JUMPER-2-NC_BY_TRACE_YES_SILK
STANDOFF1, STANDOFF2: STAND-OFF
TP1: VDD_TP; TP_15TH
U1: LSM303C; LGA-12
U2: LM3880; SOT23-6
U$8: OSHW-LOGOS; OSHW-LOGO-S

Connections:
DRDY_MAG: JP2.2, U1.11
GND: C1.C, C2.2, C3.2, C4.1, JP1.1, U1.6, U1.8, U2.2
I2C-UP: R5.2, SJ1.1
INT_MAG: JP2.6, U1.7
INT_XL: JP2.1, U1.12
unnamed: C4.2, U1.5
unnamed: R2.2, SJ1.3
SCL/SCLK: JP1.4, R2.1, U1.1
SDA/SDI/SDO: JP1.3, R5.1, U1.4
VCC: JP2.4, R1.1, SJ2.2, U2.1, U2.3
VDD: C1.A, C2.1, R1.2, TP1.P$1, U1.9, U2.6
VDD_IO: C3.1, JP1.2, R3.1, R4.1, SJ1.2, SJ2.1, U1.10
~CS_MAG: JP2.5, R4.2, U1.3
~CS_XL: JP2.3, R3.2, U1.2

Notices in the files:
parts/oomp_project_github_sparkfun_logic_level_bidirectional_logic_level_bidirectional_current/data/original/kicad_file.kicad_sch:
Released under the Creative Commons
http://creativecommons.org/licenses/by-sa/3.0
parts/oomp_project_github_sparkfun_lsm6_ds3_breakout_lsm6_ds3_breakout_current/data/kicad_file.kicad_sch:
https://creativecommons.org/licenses/by-sa/4.0
parts and their libraries:
Released under the Creative Commons Attribution Share-Alike 4.0 License
Released under the Creative Commons Attribution Share-Alike 3.0 License
